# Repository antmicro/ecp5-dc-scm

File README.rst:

============
ECP5 DC-SCM
============

Copyright (c) 2020-2024 `Antmicro <https://www.antmicro.com>`_

.. image:: https://img.shields.io/badge/View%20on-Antmicro%20Open%20Source%20Portal-332d37?style=flat-square
      :target: https://opensource.antmicro.com/projects/ecp5-dc-scm

.. figure:: img/ecp5-dc-scm.png

Overview
--------

This repository contains design files of the experimental Data Center Secure Control Module (DC-SCM).
The main purpose of this platform is to provide open-source DC-SCM with Baseboard Management Controller (BMC) unit based on Lattice ECP5 FPGA family.
The design files were prepared in KiCad.
This design is now a Work in Progress.

Repository structure
--------------------
The main repository directory contains KiCad PCB project files, a LICENSE and README.
The remaining files are stored in the following directories:

* ``img`` - contains graphics for this README
* ``doc`` - contains schematics in pdf form
* ``assets`` - contains visual assets

Key Features
------------

* ECP5 FPGA - LFE5UM5G-85F-8BG756C
* DC-SCI standard 168-pin 4C+ edge connector
* On-board DDR3 DRAM and eMMC
* QSPI FLASH memory
* Gigabit Ethernet interface with KSZ9031RNXCA transciever
* JTAG connector
* M.2 (key M) connector with PCIe x4 interface
* 13 I2C buses, 4 I3C buses
* dual UART 
* 2x USB 2.0 host/device PHY (USB3300)
* SPI connector
* RoT module connector
* TPM SPI connector
* optional external 12V power input 

Block diagram
-------------

.. figure:: img/ecp5-dc-scm-diagram.png

License
=======

`Apache-2.0 <LICENSE>`_

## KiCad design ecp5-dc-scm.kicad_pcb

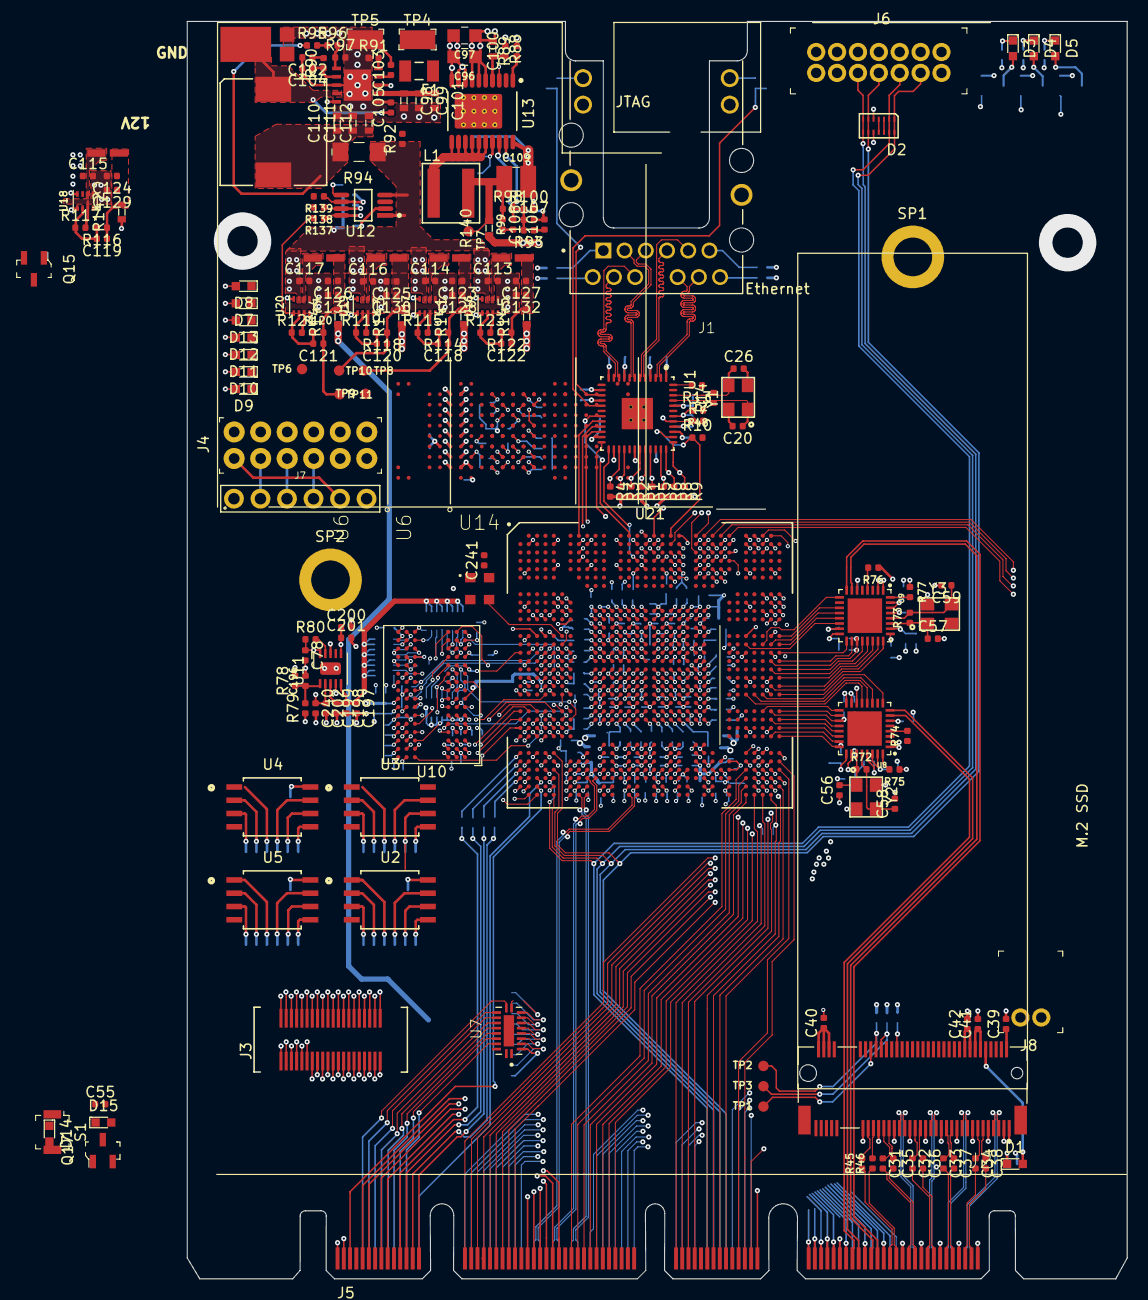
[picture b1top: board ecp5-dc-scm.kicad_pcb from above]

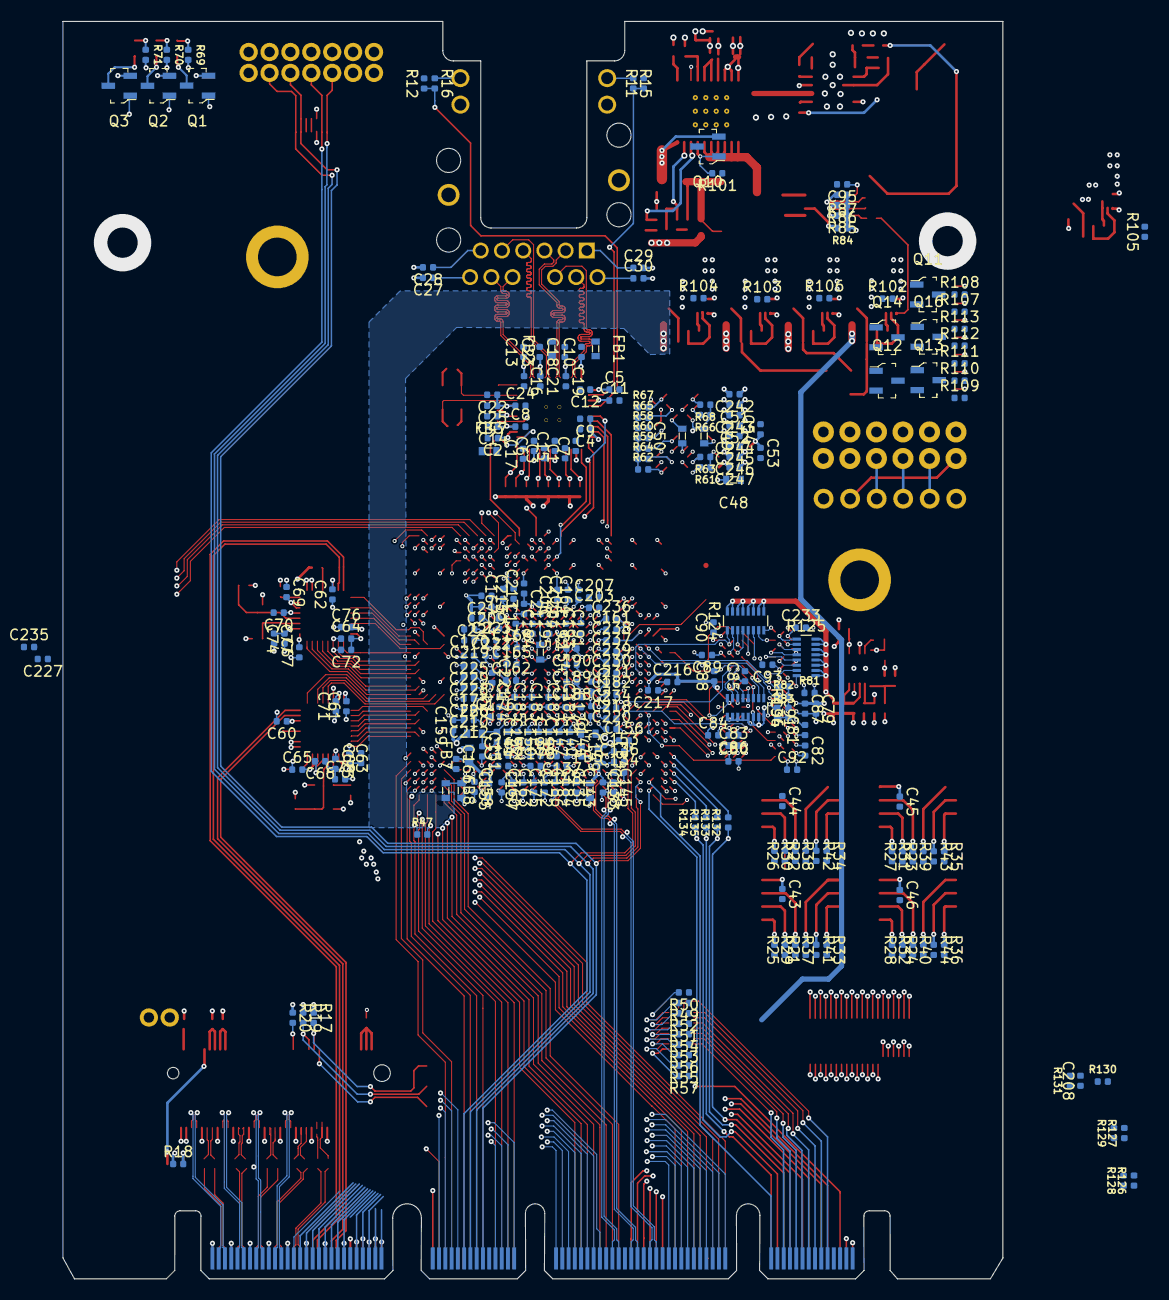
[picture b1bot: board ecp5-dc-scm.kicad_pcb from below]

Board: 8 copper layers, 90.0 x 120.4 mm, 481 parts (287 on the bottom side), 409 nets.

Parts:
C1, C6, C10, C18, C22, C53, C66, C68, C70, C72, C75, C77, C79, C134, C156, C158, C159, C160, C203, C209, C219, C225, C230, C235: C_4u7_0402; 0402-cap
C2, C3, C4, C8, C19, C43, C44, C45, C46, C80, C81, C82, C83, C84, C85, C86, C87, C89, C90, C91, C92, C135, C136, C161, C162, C163, C164, C165, C166, C167, C168, C170, C171, C173, C174, C176, C177, C179, C181, C182, C183, C184, C185, C186, C187, C188, C189, C190, C191, C192, C193, C194, C195, C204, C205, C206, C207, C210, C211, C212, C213, C214, C215, C218, C220, C221, C222, C223, C224, C226, C227, C228, C229, C231, C232, C233, C234, C236, C237, C238, C239: C_470n_0402; 0402-cap
C5, C7, C9, C11, C12, C13, C14, C15, C16, C17, C21, C23, C25, C95, C103, C138, C143, C144, C145, C146, C147, C172, C175: C_10n_0402; 0402-cap
C20, C26: C_22p_0402; 0402-cap
C24, C27, C28, C29, C30, C31, C32, C33, C34, C35, C36, C37, C38, C47, C51, C52, C54, C55, C60, C61, C62, C63, C64, C65, C67, C69, C71, C73, C74, C76, C88, C93, C94, C100, C105, C137, C139, C140, C141, C142, C169, C200, C201, C202, C208, C216, C217, C240, C241, C242, C243, C244, C245, C246, C247: C_100n_0402; 0402-cap
C39, C40, C41, C42, C78, C113, C114, C115, C116, C117, C123, C124, C125, C126, C127, C128, C129, C130, C131, C132, C197, C198, C199: C_10u_0402; 0402-cap
C48, C49, C50: C_22u_0603; 0603-cap
C56, C57, C58, C59: C_12p_0402; 0402-cap
C96, C97: C_10u_0805; 0805-cap
C98, C99, C101: C_2u2_0603_25V; 0603-cap
C102: C_4n7_0402; 0402-cap
C104: C_47p_0402; 0402-cap
C106: C_1n8_0402; 0402-cap
C107: C_180p_0402; 0402-cap
C108: C_750p_0402; 0402-res
C109: C_47u_1210; 1210-cap
C110, C111, C112, C133, C154, C155, C157: C_47u_0603; 0603-cap
C118, C119, C120, C121, C122: C_120p_0402; 0402-res
C148, C149, C150, C151, C152, C153, C178, C180, C196: C_1n_0402; 0402-res
D1: KP-1608CGCK; LED_0603
D2: TPD6E05U06
D3, D4, D5, D7, D8, D9, D10, D11, D12, D13, D14, D15: LG_L29K-G2J1-24-Z; LED_0603
D6: PDS760-13
F1: 0466003.NR; 1206-Fuse-Littelfuse-0466-0-0-MFG
FB1, FB2, FB3, FB4, FB5, FB6, FB7, FB8: BLM18PG121SN1D; 0603-res
IC1: TPS54561; WSON-10_4x4
J1: L834-1G1T-S7; BEL_L834-1G1T-S7
J2: 1-2199230-6
J3: 529910408
J4: M20-7830642; PinHeader_6x2_P2.54mm_Vertical
J5: SFF-TA-1002-4C+
J6: 0878311420; PinHeader_2x7_P2mm_Drill1mm
J7: 61300611121
J8: S2B-PH-K-S_LF__SN_; PinHeader_1x2_P2mm_Drill1mm_RA
L1: XAL5030-801; Coilcraft-XAL5030
L2: WE_7447798720
L3, L4, L5, L6, L7: IHLP1212AEERR47M11; IHLP-1212AE
Q1, Q2, Q3, Q10, Q11, Q12, Q13, Q14, Q15, Q16, Q17: 2N7002; SOT-23-3
R1, R2, R3, R4, R5, R6, R7, R8, R9, R10, R11, R12, R97: R_10k2_0402; 0402-res
R13: R_12k1_0402; 0402-res
R14: R_1M8_0402; 0402-res
R15, R16, R25, R26, R27, R28, R74, R76, R85, R86, R87, R107, R108, R109, R110, R111, R112, R113, R129, R130: R_1k_0402; 0402-res
R17, R19, R20, R29, R30, R31, R32, R33, R34, R35, R36, R37, R38, R39, R40, R41, R42, R43, R44, R58, R59, R60, R61, R62, R63, R64, R65, R66, R67, R68, R78, R79, R80, R98, R100, R101, R102, R103, R104, R105, R106, R126, R127, R131: R_10k_0402; 0402-res
R18: R_330R_0402; 0402-res
R21, R22, R23, R24, R48, R93: R_4k7_0402; 0402-res
R45, R46, R47, R132, R133, R134, R135, R137, R138, R139: R_0R_0402; 0402-res
R49, R50, R51, R52, R53, R54, R55, R56: R_357k_0402; 0402-res
R57, R116: R_200k_0402; 0402-res
R69, R70, R71, R84: R_1k1_0402; 0402-res
R72, R73: R_1M5_0402; 0402-res
R75, R77: R_12k_0402; 0402-res
R81: R_240R_0402; 0402-res
R82, R83: R_51R_0402; 0402-res
R88: R_10R_0603; 0603-res
R89: R_47k_0402; 0402-res
R90: R_16k9_0402; 0402-res
R91: R_243k_0402; 0402-res
R92, R115, R117, R119, R121, R123: R_100k_0402; 0402-res
R94: R_0R_1206; 1206-res
R95: R_49R9_0402; 0402-res
R96: R_53k6_0402; 0402-res
R99: R_470k_0402; 0402-res
R114, R122: R_453k_0402; 0402-res
R118: R_124k_0402; 0402-res
R120: R_66k5_0402; 0402-res
R124, R125, R136: 8x51R_0602_array; R_Array_Convex_8x0602
R128: R_22R_0402; 0402-res
R140, R141, R142, R143, R144, R145: R_0R_0603; 0603-res
S1: B3U-1000P; Switch_Tactile_SMD_B3U-1000P
SP1: 9774025151
SP2: 9774030151
TP1, TP2, TP3, TP6, TP7, TP8, TP9, TP10, TP11: TP_SMD1MM; Testpoint_smd_1mm
TP4, TP5: RCW-0C; PROBE_PAD_1206
U1: KSZ9031RNXCA; QFN-48-Microchip-QFN77-48LD-PL-2
U2, U3, U4, U5: W25Q32JVSSIQ_TR; W25Q32JVSSIQ
U6, U6#2: MTFC16GAPALNA-AIT; BGA100CP100_17X10_1800X1400X140B46N
U7: NVT2008DQ,115; QFN50P250X450X100-21N
U8, U9: USB3300-EZK-TR; QFN50P500X500X100-33N
U10: AS4C256M16D3; BGA-96_9.0x13.0mm_Layout2x3x16_P0.8mm
U11: TPS51200DRC; VSON-10-1EP_3x3mm
U12: LM3881MME_NOPB; VSSOP8-Texas_Instruments-DGK0008A
U13: LM21212-2; HTSSOP-20_TI-PWP
U14: AMJMEFB-100.0000T; AMJMEFB
U16, U17, U18, U19, U20: TPS62823DLCT; QFN-8_2x1mm
U21: ECP5UM5G_85_CABGA756; CABGA756_27x27mm_p0.8mm
Y1: ABM8G-25.000MHZ-18-D2Y-T; KX-7
Y2, Y3: TSX-3225; KX-7

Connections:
/DDR3/DDR3_VTT: C197.1, C198.1, C199.1, R124.9, R124.10, R124.11, R124.12, R124.13, R124.14, R124.15, R124.16, R125.9, R125.10, R125.11, R125.12, R125.13, R125.14, R125.15, R125.16, R136.9, R136.10, R136.11, R136.12, R136.13, R136.14, R136.15, R136.16, U11.3, U11.5
/Ethernet/AVDDL: C18.1, C19.1, C21.1, C23.1, FB2.1, U1.4, U1.9
/Ethernet/AVDDL_PLL: C22.1, C24.1, C25.1, FB3.1, U1.44
/Ethernet/ETH1_N: J1.10, U1.3
/Ethernet/ETH1_P: J1.11, U1.2
/Ethernet/ETH2_N: J1.5, U1.6
/Ethernet/ETH2_P: J1.4, U1.5
/Ethernet/ETH3_N: J1.2, U1.8
/Ethernet/ETH3_P: J1.3, U1.7
/Ethernet/ETH4_N: J1.9, U1.11
/Ethernet/ETH4_P: J1.8, U1.10
/Ethernet/ETH_LED1: R11.1, R15.2, U1.15
/Ethernet/ETH_LED2: R12.1, R16.2, U1.17
/FPGA power supply/VCCHTX0: C139.1, C144.1, C149.1, FB5.2, U21.AC13, U21.AC17
/FPGA power supply/VCCHTX1: C141.1, C146.1, C151.1, FB6.2, U21.AC16, U21.AC20
/Interfaces/1V0_EN: C55.2, R57.2, U7.2, U7.20
/Power supply/1V0_PG: Q11.1, R102.2, U20.8
/Power supply/1V2_PG: Q10.1, R101.2, U13.17
/Power supply/1V8_PG: Q15.1, R105.2, U18.8
/Power supply/1V35_PG: Q16.1, R106.2, U19.8
/Power supply/2V5_PG: Q14.1, R104.2, U16.8
/Power supply/3V3_PG: Q13.1, R103.2, U17.8
/Power supply/5V0_PG: IC1.10, R92.2
/Power supply/PWR_EN: Q12.1, R84.2, U12.2
/Power supply/VCCA0_EN: R137.2, U13.3, U20.1
/Power supply/VCCAUX_EN: R139.2, U16.1
/Power supply/VCCIO_EN: R138.2, U17.1, U18.1, U19.1
CLK_100M_PCIE_DN: J5.A13, U21.AM15
CLK_100M_PCIE_DP: J5.A12, U21.AM14
CLK_PCIE_x4_DN: J2.53, R46.2
CLK_PCIE_x4_DP: J2.55, R45.2
DDR3_A0: R136.1, U10.N3, U21.W4
DDR3_A1: R125.4, U10.P7, U21.V7
DDR3_A2: R124.3, U10.P3, U21.U7
DDR3_A3: R124.2, U10.N2, U21.AE6
DDR3_A4: R125.3, U10.P8, U21.R6
DDR3_A5: R124.4, U10.P2, U21.AE4
DDR3_A6: R125.2, U10.R8, U21.U6
DDR3_A7: R124.1, U10.R2, U21.U5
DDR3_A8: R125.1, U10.T8, U21.R7
DDR3_A9: R124.5, U10.R3, U21.R4
DDR3_A10: R125.7, U10.L7, U21.U4
DDR3_A11: R124.7, U10.R7, U21.T6
DDR3_A12: R125.5, U10.N7, U21.T5
DDR3_A13: R124.6, U10.T3, U21.T4
DDR3_A14: R124.8, U10.T7, U21.T7
DDR3_BA0: R136.7, U10.M2, U21.AC7
DDR3_BA1: R125.6, U10.N8, U21.V6
DDR3_BA2: R136.2, U10.M3, U21.W5
DDR3_CAS: R136.5, U10.K3, U21.W2
DDR3_CKE: R125.8, U10.K9, U21.Y1
DDR3_CLK+: R82.1, U10.J7, U21.P5
DDR3_CLK-: R83.2, U10.K7, U21.P4
DDR3_CS: R136.6, U10.L2, U21.R1
DDR3_DM0: U10.E7, U21.AD7
DDR3_DM1: U10.D3, U21.AC2
DDR3_DQ0: U10.E3, U21.AC6
DDR3_DQ1: U10.F7, U21.AD6
DDR3_DQ2: U10.F2, U21.Y4
DDR3_DQ3: U10.F8, U21.AE5
DDR3_DQ4: U10.H3, U21.AB7
DDR3_DQ5: U10.H8, U21.Y5
DDR3_DQ6: U10.G2, U21.Y6
DDR3_DQ7: U10.H7, U21.Y7
DDR3_DQ8: U10.D7, U21.AE3
DDR3_DQ9: U10.C3, U21.AE1
DDR3_DQ10: U10.C8, U21.AD3
DDR3_DQ11: U10.C2, U21.AB1
DDR3_DQ12: U10.A7, U21.AB4
DDR3_DQ13: U10.A2, U21.AC1
DDR3_DQ14: U10.B8, U21.AE2
DDR3_DQ15: U10.A3, U21.AD1
DDR3_DQS0+: U10.F3, U21.AB5
DDR3_DQS0-: U10.G3, U21.AB6
DDR3_DQS1+: U10.C7, U21.AC3
DDR3_DQS1-: U10.B7, U21.AB2
DDR3_ODT: R136.8, U10.K1, U21.AD4
DDR3_RAS: R136.4, U10.J3, U21.AB3
DDR3_RESET: U10.T2, U21.T2
DDR3_VREF: C88.1, C93.1, C200.1, C201.1, C216.2, C217.2, U10.H1, U10.M8, U11.6, U21.V4
DDR3_WE: R136.3, U10.L3, U21.AC5
DONE: R126.1, R128.1, U21.AJ4
ESPI_ALERT_N: J5.B3, U21.K30
ESPI_CLK: J5.B1, U21.L31
ESPI_CS0_N: J5.B2, U21.L32
ESPI_CS1_N: J5.B9, U21.H32
ESPI_IO0: J5.B5, U21.K32
ESPI_IO1: J5.B6, U21.K31
ESPI_IO2: J5.B7, U21.J32
ESPI_IO3: J5.B8, U21.H31
ESPI_RESET_N: J5.B4, U21.H30
ETH_INT_N: R10.1, U1.38, U21.A19
ETH_MDC: R8.1, U1.36, U21.B16
ETH_MDIO: R9.1, U1.37, U21.D17
ETH_~RESET: C47.1, R48.2, U1.42, U21.D18
GCLK100: U14.3, U21.N6
GND: C1.2, C2.2, C3.2, C4.2, C5.2, C6.2, C7.2, C8.2, C9.2, C10.2, C11.2, C12.2, C13.2, C14.2, C15.2, C16.2, C17.2, C18.2, C19.2, C20.2, C21.2, C22.2, C23.2, C24.2, C25.2, C26.2, C27.2, C28.2, C29.2, C30.2, C39.2, C40.2, C41.2, C42.2, C43.2, C44.2, C45.2, C46.2, C47.2, C48.2, C49.2, C50.2, C51.2, C52.2, C53.2, C54.2, C55.1, C56.2, C57.2, C58.2, C59.2, C60.1, C61.1, C62.1, C63.1, C64.1, C65.1, C66.1, C67.1, C68.2, C69.1, C70.1, C71.1, C72.2, C73.1, C74.1, C75.2, C76.1, C77.2, C78.2, C79.2, C80.2, C81.2, C82.2, C83.2, C84.2, C85.2, C86.2, C87.2, C88.2, C89.2, C90.2, C91.2, C92.2, C93.2, C94.1, C95.2, C96.2, C97.2, C98.2, C99.2, C100.2, C101.2, C102.2, C103.2, C104.2, C109.2, C110.2, C111.2, C112.2, C113.2, C114.2, C115.2, C116.2, C117.2, C123.2, C124.2, C125.2, C126.2, C127.2, C128.2, C129.2, C130.2, C131.2, C132.2, C133.2, C134.2, C135.2, C136.2, C137.2, C138.2, C139.2, C140.2, C141.2, C142.2, C143.2, C144.2, C145.2, C146.2, C147.2, C148.2, C149.2, C150.2, C151.2, C152.2, C153.2, C154.2, C155.2, C156.2, C157.2, C158.2, C159.2, C160.2, C161.2, C162.2, C163.2, C164.2, C165.2, C166.2, C167.2, C168.2, C169.2, C170.2, C171.2, C172.2, C173.2, C174.2, C175.2, C176.2, C177.2, C178.2, C179.2, C180.2, C181.2, C182.2, C183.2, C184.2, C185.2, C186.2, C187.2, C188.2, C189.2, C190.2, C191.2, C192.2, C193.2, C194.2, C195.2, C196.2, C197.2, C198.2, C199.2, C200.2, C201.2, C202.2, C203.2, C204.2, C205.2, C206.2, C207.2, C208.1, C209.2, C210.2, C211.2, C212.2, C213.2, C214.2, C215.2, C216.1, C217.1, C218.2, C219.2, C220.2, C221.2, C222.2, C223.2, C224.2, C225.2, C226.2, C227.2, C228.2, C229.2, C230.2, C231.2, C232.2, C233.2, C234.2, C235.2, C236.2, C237.2, C238.2, C239.2, C240.2, C241.2, C242.2, C243.2, C244.2, C245.2, C246.2, C247.2, D2.5, D2.10, D6.A, IC1.8, IC1.11, J1.13, J1.15, J1.S1, J1.S2, J2.1, J2.3, J2.9, J2.15, J2.21, J2.27, J2.33, J2.39, J2.45, J2.51, J2.57, J2.71, J2.73, J2.75, J2.SH1, J2.SH2, J3.1, J4.5, J4.11, J5.A11, J5.A14, J5.A17, J5.A20, J5.A33, J5.A42, J5.A58, J5.A61, J5.A64, J5.A67, J5.A70, J5.B10, J5.B17, J5.B26, J5.B33, J5.B38, J5.B49, J5.B52, J5.B55, J5.B58, J5.B61, J5.B64, J5.B67, J5.B70, J5.OA3, J5.OA4, J5.OA13, J5.OB4, J5.OB7, J5.OB10, J6.1, J6.3, J6.5, J6.7, J6.9, J6.11, J6.13, J7.6, J8.2, Q1.2, Q2.2, Q3.2, Q10.2, Q11.2, Q12.2, Q13.2, Q14.2, Q15.2, Q16.2, Q17.2, R13.1, R75.1, R77.1, R78.2, R81.2, R89.2, R91.1, R97.2, R100.2, R115.2, R117.2, R119.2, R121.2, R123.2, S1.2, TP5.1, U1.29, U1.49, U2.4, U3.4, U4.4, U5.4, U6#2.G2, U6#2.G3, U6#2.G4, U6#2.G5, U6#2.G6, U6#2.G7, U6#2.G8, U6#2.G9, U6#2.H2, U6#2.H9, U6#2.J5, U6#2.L3, U6#2.L8, U6#2.M4, U6#2.M7, U6#2.P2, U6#2.P9, U7.1, U8.1, U8.2, U8.33, U9.1, U9.2, U9.33, U10.A9, U10.B1, U10.B3, U10.B9, U10.D1, U10.D8, U10.E1, U10.E2, U10.E8, U10.F9, U10.G1, U10.G8, U10.G9, U10.J2, U10.J8, U10.M1, U10.M9, U10.P1, U10.P9, U10.T1, U10.T9, U11.4, U11.8, U11.11, U12.3, U13.8, U13.9, U13.10, U13.20, U13.21, U14.2, U16.3, U16.5, U17.3, U17.5, U18.3, U18.5, U19.3, U19.5, U20.3, U20.5, U21.AA11, U21.AA22, U21.AB11, U21.AB12, U21.AB13, U21.AB14, U21.AB15, U21.AB16, U21.AB17, U21.AB18, U21.AB19, U21.AB20, U21.AB21, U21.AB22, U21.AC12, U21.AC21, U21.AD2, U21.AD5, U21.AD28, U21.AD31, U21.AF11, U21.AF12, U21.AF14, U21.AF15, U21.AF16, U21.AF17, U21.AF19, U21.AF20, U21.AF23, U21.AG11, U21.AG14, U21.AG15, U21.AG16, U21.AG17, U21.AG20, U21.AG23, U21.AH2, U21.AH5, U21.AH7, U21.AH8, U21.AH11, U21.AH14, U21.AH15, U21.AH16, U21.AH17, U21.AH20, U21.AH23, U21.AH24, U21.AH25, U21.AH26, U21.AH29, U21.AH31, U21.AJ7, U21.AJ8, U21.AJ11, U21.AJ14, U21.AJ17, U21.AJ20, U21.AJ23, U21.AJ26, U21.AK7, U21.AK8, U21.AK11, U21.AK14, U21.AK17, U21.AK20, U21.AK23, U21.AK26, U21.AL2, U21.AL5, U21.AL7, U21.AL8, U21.AL9, U21.AL11, U21.AL12, U21.AL14, U21.AL15, U21.AL17, U21.AL18, U21.AL20, U21.AL21, U21.AL23, U21.AL24, U21.AL26, U21.AL29, U21.AL31, U21.AM7, U21.AM26, U21.B2, U21.B5, U21.B9, U21.B13, U21.B15, U21.B18, U21.B20, U21.B24, U21.B28, U21.B31, U21.C30, U21.E2, U21.E5, U21.E9, U21.E13, U21.E15, U21.E18, U21.E20, U21.E24, U21.E28, U21.E31, U21.J2, U21.J5, U21.J28, U21.J31, U21.K10, U21.K11, U21.K22, U21.K23, U21.L10, U21.L11, U21.L12, U21.L13, U21.L14, U21.L15, U21.L16, U21.L17, U21.L18, U21.L19, U21.L20, U21.L21, U21.L22, U21.L23, U21.M11, U21.M22, U21.N2, U21.N5, U21.N11, U21.N13, U21.N14, U21.N15, U21.N16, U21.N17, U21.N18, U21.N19, U21.N20, U21.N22, U21.N28, U21.N31, U21.P11, U21.P13, U21.P14, U21.P15, U21.P16, U21.P17, U21.P18, U21.P19, U21.P20, U21.P22, U21.R2, U21.R5, U21.R11, U21.R13, U21.R14, U21.R15, U21.R16, U21.R17, U21.R18, U21.R19, U21.R20, U21.R22, U21.R28, U21.R31, U21.T11, U21.T13, U21.T14, U21.T15, U21.T16, U21.T17, U21.T18, U21.T19, U21.T20, U21.T22, U21.U11, U21.U13, U21.U14, U21.U15, U21.U16, U21.U17, U21.U18, U21.U19, U21.U20, U21.U22, U21.V2, U21.V5, U21.V11, U21.V13, U21.V14, U21.V15, U21.V16, U21.V17, U21.V18, U21.V19, U21.V20, U21.V22, U21.V28, U21.V31, U21.W11, U21.W13, U21.W14, U21.W15, U21.W16, U21.W17, U21.W18, U21.W19, U21.W20, U21.W22, U21.Y2, U21.Y11, U21.Y13, U21.Y14, U21.Y15, U21.Y16, U21.Y17, U21.Y18, U21.Y19, U21.Y20, U21.Y22, U21.Y31, Y1.2, Y1.4, Y2.2, Y2.4, Y3.2, Y3.4
I2C[0]_SCL: J5.A1, U21.E25
I2C[0]_SDA: J5.A2, U21.D26
I2C[1]_SCL: J5.A3, U21.E22
I2C[1]_SDA: J5.A4, U21.E23
I2C[2]_SCL: J5.A5, U21.D22
I2C[2]_SDA: J5.A6, U21.D23
I2C[3]_SCL: J5.A7, U21.D25
I2C[3]_SDA: J5.A8, U21.D24
I2C[4]_SCL: J5.A9, U21.C26
I2C[4]_SDA: J5.A10, U21.B29
I2C[5]_SCL: J5.A21, U21.A31
I2C[5]_SDA: J5.A22, U21.B30
I2C[6]_SCL: J5.A23, U21.A30
I2C[6]_SDA: J5.A24, U21.A29
I2C[7]_SCL: J5.A25, U21.A28
I2C[7]_SDA: J5.A26, U21.C25
I2C[8]_SCL: J5.A27, U21.B25
I2C[8]_SDA: J5.A28, U21.B26
I2C[9]_SCL: J5.A29, U21.C23
I2C[9]_SDA: J5.A30, U21.C24
I2C[10]_SCL: J5.A31, U21.B23
I2C[10]_SDA: J5.A32, U21.B22
I2C[11]_SCL: J5.A38, U21.A26
I2C[11]_SDA: J5.A39, U21.A25
I2C[12]_SCL: J5.A40, U21.A24
I2C[12]_SDA: J5.A41, U21.A23
I3C[0]_SCL_1V0: J5.OA5, U7.11
I3C[0]_SCL_3V3: R50.2, U7.10, U21.A20
I3C[0]_SDA_1V0: J5.OA6, U7.12
I3C[0]_SDA_3V3: R49.2, U7.9, U21.C19
I3C[1]_SCL_1V0: J5.OA7, U7.13
I3C[1]_SCL_3V3: R52.2, U7.8, U21.F20
I3C[1]_SDA_1V0: J5.OA8, U7.14
I3C[1]_SDA_3V3: R51.2, U7.7, U21.D19
I3C[2]_SCL_1V0: J5.OA9, U7.15
I3C[2]_SCL_3V3: R54.2, U7.6, U21.E19
I3C[2]_SDA_1V0: J5.OA10, U7.16
I3C[2]_SDA_3V3: R53.2, U7.5, U21.F19
I3C[3]_SCL_1V0: J5.OA11, U7.17
I3C[3]_SCL_3V3: R56.2, U7.4, U21.D20
I3C[3]_SDA_1V0: J5.OA12, U7.18
I3C[3]_SDA_3V3: R55.2, U7.3, U21.C20
INIT_N: D14.2, J3.19, R127.1, U21.AG4
JTAG_TCK: D2.13, J5.A34, J6.6, U21.AK5
JTAG_TDI: D2.8, J5.A36, J6.10, U21.AJ5
JTAG_TDO: D2.9, J5.A37, J6.8, U21.AG5
JTAG_TMS: D2.14, J5.A35, J6.4, U21.AM5
MMC_CLK: R58.2, U6#2.P6, U21.P6
MMC_CMD: R60.2, U6#2.P5, U21.J7
MMC_DAT0: R61.2, U6#2.K2, U21.N4
MMC_DAT1: R62.2, U6#2.N2, U21.L7
MMC_DAT2: R63.2, U6#2.K3, U21.N3
MMC_DAT3: R64.2, U6#2.N3, U21.L4
MMC_DAT4: R65.2, U6#2.N8, U21.K7
MMC_DAT5: R66.2, U6#2.K8, U21.K5
MMC_DAT6: R67.2, U6#2.N9, U21.K6
MMC_DAT7: R68.2, U6#2.K9, U21.J6
MMC_RSTN: R59.2, U6#2.M5, U21.L3
NCSI_CLK: J5.B18, U21.AJ28
NCSI_CRS_DV: J5.B19, U21.AK28
NCSI_RXD0: J5.B24, U21.AJ29
NCSI_RXD1: J5.B25, U21.AK29
NCSI_RXER: J5.B23, U21.AH30
NCSI_TXD0: J5.B21, U21.AM28
NCSI_TXD1: J5.B22, U21.AH28
NCSI_TXEN: J5.B20, U21.AL28
unnamed: C10.1, C13.1, C16.1, FB1.2, U1.1, U1.12
unnamed: C20.1, R14.1, U1.45, Y1.1
unnamed: C26.1, R14.2, U1.46, Y1.3
unnamed: C27.1, J1.12
unnamed: C28.1, J1.6
unnamed: C29.1, J1.1
unnamed: C30.1, J1.7
unnamed: C31.1, J2.49
unnamed: C32.1, J2.37
unnamed: C33.1, J2.25
unnamed: C34.1, J2.13
unnamed: C35.1, J2.47
unnamed: C36.1, J2.35
unnamed: C37.1, J2.23
unnamed: C38.1, J2.11
unnamed: C53.1, C54.1, U6#2.E4
unnamed: C56.1, R72.1, U8.27, Y2.1
unnamed: C57.1, R73.1, U9.27, Y3.1
unnamed: C58.1, R72.2, U8.28, Y2.3
unnamed: C59.1, R73.2, U9.28, Y3.3
unnamed: C66.2, U8.29
unnamed: C70.2, U9.29
unnamed: C94.2, R82.2, R83.1
unnamed: C95.1, U12.5
unnamed: C100.1, R88.2, U13.4
unnamed: C102.1, R90.2
unnamed: C103.1, IC1.4
unnamed: C104.1, IC1.7, R90.1
unnamed: C105.1, D6.C, IC1.9, L2.1
unnamed: C105.2, IC1.1
unnamed: C106.1, R93.1
unnamed: C106.2, C107.2, U13.18
unnamed: C107.1, R93.2, R98.2, R99.2, R100.1, U13.19
unnamed: C108.1, C109.1, L1.2, R98.1, R140.2, TP7.1
unnamed: C108.2, R99.1
unnamed: C110.1, C111.1, C112.1, L2.2, R94.2, R95.1
unnamed: C118.1, C123.1, C128.1, L3.2, R114.1, R141.2, TP8.1
unnamed: C118.2, R114.2, R115.1, U17.2
unnamed: C119.1, C124.1, C129.1, L4.2, R116.1, R142.2, TP9.1
unnamed: C119.2, R116.2, R117.1, U18.2
unnamed: C120.1, C125.1, C130.1, L5.2, R118.1, R143.2, TP10.1
unnamed: C120.2, R118.2, R119.1, U19.2
unnamed: C121.1, C126.1, C131.1, L6.2, R120.2, R144.2, TP11.1
unnamed: C121.2, R120.1, R121.1, U20.2
unnamed: C122.1, C127.1, C132.1, L7.2, R122.1, R145.2
unnamed: C122.2, R122.2, R123.1, U16.2
unnamed: C196.1, R78.1, R79.2, U11.1
unnamed: D1.1, R18.2
unnamed: D1.2, J2.10
unnamed: D3.1, R69.1
unnamed: D3.2, Q1.3
unnamed: D4.1, R70.1
unnamed: D4.2, Q2.3
unnamed: D5.1, R71.1
unnamed: D5.2, Q3.3
unnamed: D7.2, R107.2
unnamed: D8.2, R108.2
unnamed: D9.2, R109.2
unnamed: D10.2, R110.2
unnamed: D11.2, R111.2
unnamed: D12.2, R112.2
unnamed: D13.2, R113.2
unnamed: D14.1, R129.2
unnamed: D15.1, R130.2
unnamed: D15.2, Q17.3
unnamed: IC1.3, TP6.1
unnamed: IC1.5, R91.2
unnamed: IC1.6, R96.2, R97.1
unnamed: J1.14, R15.1
unnamed: J1.16, R16.1
unnamed: J2.44, R20.2
unnamed: J2.52, R17.2, TP2.1
unnamed: J2.54, TP1.1
unnamed: J5.B56, R45.1
unnamed: J5.B57, R46.1
unnamed: L1.1, U13.11, U13.12, U13.13, U13.14, U13.15, U13.16
unnamed: L3.1, U17.6
unnamed: L4.1, U18.6
unnamed: L5.1, U19.6
unnamed: L6.1, U20.6
unnamed: L7.1, U16.6
unnamed: Q10.3, R107.1
unnamed: Q11.3, R108.1
unnamed: Q12.3, R109.1
unnamed: Q13.3, R110.1
unnamed: Q14.3, R111.1
unnamed: Q15.3, R112.1
unnamed: Q16.3, R113.1
unnamed: Q17.1, R128.2
unnamed: R13.2, U1.48
unnamed: R74.2, U8.4
unnamed: R75.2, U8.32
unnamed: R76.2, U9.4
unnamed: R77.2, U9.32
unnamed: R80.2, U11.9
unnamed: R81.1, U10.L8
unnamed: R89.1, U13.1
unnamed: R95.2, R96.1
unnamed: R132.2, U21.AG1
unnamed: R133.2, U21.AH1
unnamed: R134.2, U21.AK1
unnamed: R135.2, U21.AJ1
unnamed: R85.2, R137.1, U12.8
unnamed: R86.2, R138.1, U12.7
unnamed: R87.2, R139.1, U12.6
P12V_AUX: F1.1, J5.OA1, J5.OA2, J5.OB1, J5.OB2
PCIE_BMC_RX_DN: J5.A19, U21.AM9
PCIE_BMC_RX_DP: J5.A18, U21.AM8
PCIE_BMC_TX_DN: J5.A16, U21.AK10
PCIE_BMC_TX_DP: J5.A15, U21.AK9
PCIE_HPM_RXN[0]: J2.41, J5.A60
PCIE_HPM_RXN[1]: J2.29, J5.A63
PCIE_HPM_RXN[2]: J2.17, J5.A66
PCIE_HPM_RXN[3]: J2.5, J5.A69
PCIE_HPM_RXP[0]: J2.43, J5.A59
PCIE_HPM_RXP[1]: J2.31, J5.A62
PCIE_HPM_RXP[2]: J2.19, J5.A65
PCIE_HPM_RXP[3]: J2.7, J5.A68
PCIE_HPM_TXN[0]: C35.2, J5.B60
PCIE_HPM_TXN[1]: C36.2, J5.B63
PCIE_HPM_TXN[2]: C37.2, J5.B66
PCIE_HPM_TXN[3]: C38.2, J5.B69
PCIE_HPM_TXP[0]: C31.2, J5.B59
PCIE_HPM_TXP[1]: C32.2, J5.B62
PCIE_HPM_TXP[2]: C33.2, J5.B65
PCIE_HPM_TXP[3]: C34.2, J5.B68
PROGRAM_N: C208.2, J3.18, R131.1, S1.1, U21.AH4
PRSNT0_N: J2.50, J5.OB3, R19.2, TP3.1, U21.AL3
QSPI0_CLK: J3.7, J5.B11
QSPI0_CS0_N: J3.8, J5.B12
QSPI0_CS1_N: J3.22, J5.B42
QSPI0_D0: J3.9, J5.B13
QSPI0_D1: J3.10, J5.B14
QSPI0_D2: J3.11, J5.B15
QSPI0_D3: J3.12, J5.B16
QSPI1_CLK: J5.B43, U21.AJ31
QSPI1_CS0_N: J5.B44, U21.AK32
QSPI1_D0: J5.B45, U21.AG28
QSPI1_D1: J5.B46, U21.AG29
QSPI1_D2: J5.B47, U21.AG30
QSPI1_D3: J5.B48, U21.AG32
QSPIA1_CS_N: J3.4, R24.2, U5.1
QSPIA1_D0: J3.6, R32.1, U5.5
QSPIA1_D1: J3.3, R44.1, U5.2
QSPIA1_D2: J3.2, R36.1, U5.3
QSPIA1_D3: J3.5, R40.1, U5.7
QSPIA2_CS_N: J3.25, R23.2, U4.1
QSPIA2_D0: J3.28, R31.1, U4.5
QSPIA2_D1: J3.24, R43.1, U4.2
QSPIA2_D2: J3.23, R35.1, U4.3
QSPIA2_D3: J3.26, R39.1, U4.7
QSPIA_CLK: J3.27, R27.2, R28.2, U4.6, U5.6
QSPIB1_CS_N: J3.31, R22.2, U3.1
QSPIB1_D0: J3.33, R30.1, U3.5
QSPIB1_D1: J3.30, R42.1, U3.2
QSPIB1_D2: J3.29, R34.1, U3.3
QSPIB1_D3: J3.32, R38.1, U3.7
QSPIB2_CS_N: J3.36, R21.2, U2.1
QSPIB2_D0: J3.39, R29.1, U2.5
QSPIB2_D1: J3.35, R41.1, U2.2
QSPIB2_D2: J3.34, R33.1, U2.3
QSPIB2_D3: J3.37, R37.1, U2.7
QSPIB_CLK: J3.38, R25.2, R26.2, U2.6, U3.6
RGMII_REF_CLK: R7.1, U1.41, U21.B17
RGMII_RXD0: R1.1, U1.32, U21.A16
RGMII_RXD1: R2.1, U1.31, U21.D16
RGMII_RXD2: R3.1, U1.28, U21.E16
RGMII_RXD3: R4.1, U1.27, U21.C8
RGMII_RX_CLK: R6.1, U1.35, U21.A17
RGMII_RX_DV: R5.1, U1.33, U21.C16
RGMII_TXD0: U1.19, U21.A14
RGMII_TXD1: U1.20, U21.A8
RGMII_TXD2: U1.21, U21.B8
RGMII_TXD3: U1.22, U21.D8
RGMII_TX_CLK: U1.24, U21.C17
RGMII_TX_EN: U1.25, U21.D15
ROT_QSPI_CS_N: J3.40, U21.AG3
ROT_QSPI_DQ0: J3.17, U21.AK2
ROT_QSPI_DQ1: J3.16, U21.AJ2
ROT_QSPI_DQ2: J3.15, U21.AM2
ROT_QSPI_DQ3: J3.14, U21.AL1
ROT_QSPI_SCK: J3.13, U21.AM3
SGPIO0_CLK: J5.B30, R47.2, U21.AK30
SGPIO0_DI: J5.B31, U21.AM30
SGPIO0_DO: J5.B29, U21.AM29
SGPIO0_LD: J5.B32, U21.AL30
SGPIO1_CLK: J5.B35, R47.1, U21.AM31
SGPIO1_DI: J5.B36, U21.AK31
SGPIO1_DO: J5.B34, U21.AJ30
SGPIO1_LD: J5.B37, U21.AL32
SGPIO_INTR_N: J5.B40, U21.AH32
SGPIO_RESET_N: J5.B39, U21.AJ32
SPI0_CLK: J4.4, J5.OB11, J7.4, R132.1
SPI0_CS_N: J4.1, J5.OB12, J7.5, R133.1
SPI0_MISO: J4.3, J5.OB14, J7.3, R135.1
SPI0_MOSI: J4.2, J5.OB13, J7.2, R134.1
UART0_SCM_RX: J5.OB9, U21.F25
UART0_SCM_TX: J5.OB8, U21.F24
UART1_SCM_RX: J5.OB6, U21.F23
UART1_SCM_TX: J5.OB5, U21.F22
ULPI1_CLKO: U9.14, U21.P28
ULPI1_D0: U9.24, U21.W31
ULPI1_D1: U9.23, U21.W32
ULPI1_D2: U9.22, U21.V32
ULPI1_D3: U9.21, U21.U31
ULPI1_D4: U9.20, U21.U32
ULPI1_D5: U9.19, U21.T31
ULPI1_D6: U9.18, U21.T32
ULPI1_D7: U9.17, U21.R32
ULPI1_DIR: U9.12, U21.P31
ULPI1_NXT: U9.11, U21.N32
ULPI1_RESET: U9.9, U21.P30
ULPI1_STP: U9.13, U21.P32
ULPI2_CLKO: U8.14, U21.R26
ULPI2_D0: U8.24, U21.AE32
ULPI2_D1: U8.23, U21.AE31
ULPI2_D2: U8.22, U21.AD32
ULPI2_D3: U8.21, U21.AC31
ULPI2_D4: U8.20, U21.AC32
ULPI2_D5: U8.19, U21.AB31
ULPI2_D6: U8.18, U21.AB32
ULPI2_D7: U8.17, U21.AB30
ULPI2_NXT: U8.11, U21.Y30
ULPI2_RESET: U8.9, U21.Y32
ULPI2_STP: U8.13, U21.Y28
ULPI_DIR: U8.12, U21.Y29
USB1_DN: J5.B54, U9.8
USB1_DP: J5.B53, U9.7
USB2_DN: J5.B51, U8.8
USB2_DP: J5.B50, U8.7
USR_LED0: Q1.1, U21.B19
USR_LED1: Q2.1, U21.C22
USR_LED2: Q3.1, U21.A22
VCC1V0: R102.1, R144.1, U7.19
VCC1V2: C1.1, C2.1, C3.1, C4.1, C5.1, C7.1, C9.1, C12.1, C15.1, C154.1, C156.1, C159.1, C162.1, C165.1, C168.1, C171.1, C174.1, C177.1, C181.1, C183.1, C185.1, C187.1, C188.1, C189.1, C190.1, C191.1, C192.1, C193.1, C194.1, C195.1, FB2.2, FB3.2, FB4.1, FB5.1, FB6.1, FB7.2, R101.1, R140.1, U1.14, U1.23, U1.26, U1.30, U1.39, U21.AA12, U21.AA13, U21.AA14, U21.AA15, U21.AA16, U21.AA17, U21.AA18, U21.AA19, U21.AA20, U21.AA21, U21.M12, U21.M13, U21.M14, U21.M15, U21.M16, U21.M17, U21.M18, U21.M19, U21.M20, U21.M21, U21.N12, U21.N21, U21.P12, U21.P21, U21.R12, U21.R21, U21.T12, U21.T21, U21.U12, U21.U21, U21.V12, U21.V21, U21.W12, U21.W21, U21.Y12, U21.Y21
VCC1V8: C71.2, C73.2, C74.2, C75.1, C76.2, C77.1, C219.1, C221.1, C222.1, C223.1, C224.1, R20.1, R105.1, R142.1, U8.15, U8.26, U9.15, U9.26, U21.M23, U21.P23, U21.R23, U21.T23
VCC1V35: C79.1, C80.1, C81.1, C82.1, C83.1, C84.1, C85.1, C86.1, C87.1, C89.1, C90.1, C91.1, C92.1, C202.1, C230.1, C231.1, C232.1, C233.1, C234.1, C240.1, R79.1, R106.1, R143.1, U10.A1, U10.A8, U10.B2, U10.C1, U10.C9, U10.D2, U10.D9, U10.E9, U10.F1, U10.G7, U10.H2, U10.H9, U10.K2, U10.K8, U10.N1, U10.N9, U10.R1, U10.R9, U11.2, U21.AA10, U21.U10, U21.V10, U21.W10
VCC2V5: FB8.2, R104.1, R145.1
VCC3V3: C6.1, C8.1, C11.1, C14.1, C17.1, C39.1, C40.1, C41.1, C42.1, C43.1, C44.1, C45.1, C46.1, C48.1, C49.1, C50.1, C51.1, C52.1, C60.2, C61.2, C62.2, C63.2, C64.2, C65.2, C67.2, C68.1, C69.2, C72.1, C78.1, C203.1, C204.1, C205.1, C206.1, C207.1, C209.1, C210.1, C211.1, C212.1, C213.1, C214.1, C215.1, C218.1, C220.1, C225.1, C226.1, C227.1, C228.1, C229.1, C235.1, C236.1, C237.1, C238.1, C239.1, C242.1, C243.1, C244.1, C245.1, C246.1, C247.1, D7.1, D8.1, D9.1, D10.1, D11.1, D12.1, D13.1, FB1.1, J2.2, J2.4, J2.12, J2.14, J2.16, J2.18, J2.70, J2.72, J2.74, J3.21, J4.6, J4.12, J6.2, J7.1, R1.2, R2.2, R3.2, R4.2, R5.2, R6.2, R7.2, R8.2, R9.2, R10.2, R11.2, R12.2, R17.1, R18.1, R19.1, R21.1, R22.1, R23.1, R24.1, R25.1, R26.1, R27.1, R28.1, R29.2, R30.2, R31.2, R32.2, R33.2, R34.2, R35.2, R36.2, R37.2, R38.2, R39.2, R40.2, R41.2, R42.2, R43.2, R44.2, R48.1, R49.1, R50.1, R51.1, R52.1, R53.1, R54.1, R55.1, R56.1, R57.1, R58.1, R59.1, R60.1, R61.1, R62.1, R63.1, R64.1, R65.1, R66.1, R67.1, R68.1, R69.2, R70.2, R71.2, R80.1, R103.1, R126.2, R127.2, R129.1, R130.1, R131.2, R141.1, U1.16, U1.34, U1.40, U2.8, U3.8, U4.8, U5.8, U6#2.F2, U6#2.F3, U6#2.F4, U6#2.F5, U6#2.F6, U6#2.F7, U6#2.F8, U6#2.F9, U6#2.H3, U6#2.H8, U6#2.L2, U6#2.L4, U6#2.L7, U6#2.L9, U6#2.P3, U6#2.P8, U8.6, U8.16, U8.25, U8.30, U8.31, U9.6, U9.16, U9.25, U9.30, U9.31, U11.10, U14.1, U21.AA23, U21.AB10, U21.AB23, U21.AC10, U21.AC23, U21.K12, U21.K14, U21.K15, U21.K16, U21.K17, U21.K18, U21.K19, U21.K21, U21.M10, U21.P10, U21.R10, U21.T10, U21.U23, U21.V23, U21.W23
VCC3V3_T: C241.1, U14.4
VCC5V0: C96.1, C97.1, C113.1, C114.1, C115.1, C116.1, C117.1, R74.1, R76.1, R84.1, R85.1, R86.1, R87.1, R88.1, R92.1, R94.1, U12.1, U12.4, U13.5, U13.6, U13.7, U16.7, U17.7, U18.7, U19.7, U20.7
VCC12V: C98.1, C99.1, C101.1, F1.2, IC1.2, TP4.1
VCCA0: C133.1, C134.1, C135.1, C136.1, C137.1, C138.1, C140.1, C143.1, C145.1, C148.1, C150.1, C153.1, FB4.2, U21.AC14, U21.AC18, U21.AG9, U21.AG12, U21.AH9, U21.AH12, U21.AJ9, U21.AJ10, U21.AJ12, U21.AJ13
VCCA1: C142.1, C147.1, C152.1, C157.1, C160.1, C163.1, C166.1, C169.1, C172.1, C175.1, C178.1, C180.1, FB7.1, U21.AC15, U21.AC19, U21.AF22, U21.AG19, U21.AG22, U21.AH19, U21.AH22, U21.AJ18, U21.AJ19, U21.AJ21, U21.AJ22
VCCAUX: C155.1, C158.1, C161.1, C164.1, C167.1, C170.1, C173.1, C176.1, C179.1, C182.1, C184.1, C186.1, FB8.1, U21.AC11, U21.AC22, U21.AJ15, U21.AJ16, U21.AJ24, U21.AJ25, U21.K13, U21.K20, U21.N10, U21.N23, U21.Y10, U21.Y23
VIRTUAL_RESEAT: J5.OA14, U21.AK3

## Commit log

2020-12-01 Add basic README.rst
2020-12-01 Create project
2020-12-01 Add gitignore
2020-12-01 Add FPGA banks schematic
2020-12-02 Add FPGA power supply sheet
2020-12-03 Add ethernet schematic sheet
2020-12-03 Clean up designators
2020-12-04 Add power-supply schematic sheet-WIP
2020-12-07 Add missing components
2020-12-07 Change power supply schematic - WIP
2020-12-07 Connect RGMII to FPGA
2020-12-07 Update main schematic file
2020-12-07 Add DDR3 schematic sheet
2020-12-07 Connect DDR3 to FPGA
2020-12-08 Added flash, added interface labels to FPGA banks sheet
2020-12-08 Added Interfaces sheet for debug and other IO connectors
2020-12-08 Add edge connector sheet
2020-12-09 Cleaned up connections
2020-12-09 Added draft sheet for RoT connector
2020-12-09 Added M.2 connector
2020-12-10 Add 1V0 power supply and sequencer
2020-12-10 SPI and QSPI mostly done (to be verified)
2020-12-10 Fix capacitors reference
2020-12-10 Added preliminary power sequencer for RoT, HPM and FPGA
2020-12-10 Add I3C voltage level translation
2020-12-11 Edit in power sequencer
2020-12-11 Add PCB outline
2020-12-12 Fix I3C labels names
2020-12-12 Add initial component placement
2020-12-12 Added TPM SPI connector
2020-12-13 Update PCB layout
2020-12-13 Clean up main schematic file
2020-12-13 Update power-supply sheet
2020-12-13 Replace DDR3 memory
2020-12-13 Removed inverters
2020-12-13 Moved eSPI interface
2020-12-13 Updated supplies connections
2020-12-14 Clean up main sch file
    Separate power supply schematic
2020-12-14 Update all schematic designators
2020-12-14 Fix designators
2020-12-14 Add ethernet and power supply component placement
2020-12-14 Fix outline
2020-12-14 Close PCB outline
2020-12-14 Add flash components placement
2020-12-14 Add DDR3 passives initial placement
2020-12-15 Added block diagram
2020-12-15 Updated outline and 3D models
2020-12-15 Added 3D vis
2020-12-15 Add local component libraries.
2020-12-15 Updated 3D vis
2020-12-15 Updated PCIe connection
2020-12-15 Diagram update
2020-12-15 README: minor fix
2020-12-15 Add power supply placement and initial routing
2020-12-15 Remove DC jack connector
2020-12-16 Add changes to power supply sheet
    Added 1k pullup to 3V3 on PWR_EN signal
    Tied PWR_EN directly to its transistor’s gate, removed 10k pullup there
    R69 package changed to 1206
    Replaced DC jack with RCW-0C testpads (1206), tied P12V_AUX with 12V0
2020-12-16 Combine two power supply sheets into one
2020-12-16 1v2 power supply component placement
2020-12-16 Add PCIe passives placement
2020-12-17 Remove I2C and I3C goldpin connectors
2020-12-17 Add power supply component placement -WIP
2020-12-17 Add component placement-power supply
2020-12-18 Add functional pins handling
2020-12-18 Segregate decoupling capacitors
2020-12-20 Add decoupling capacitors placement and re-annotate
2020-12-21 Add DDR3 breakout and change its connection to FPGA
2020-12-21 Update RoT connector pinout
2020-12-22 Add USB host circuit
2020-12-23 Add PCIex4 clk signals filtration and standoff
2020-12-26 Add USB client and eMMC to schematic
2020-12-27 Add SPI Flash pin markings and connect SGPIO1_CLK
2020-12-27 Fix SGPIOlabels
2020-12-27 Fix VCC1V2 labels and add missing resistor
2020-12-28 Connect SPI0 to FPGA through 0R
2020-12-28 Add interface tabele and fix pin labels
2020-12-28 Add component placement
2020-12-28 Update diagram and visualisation
2020-12-28 Update component libraries
2020-12-29 Add user LEDs
2020-12-29 Fix power supply labels and power sequencing
2020-12-29 Update table and add minor changes
2020-12-29 Fix sequencing transistors connection
2020-12-29 Add 1nF capacitor
2020-12-29 Reconnect RGMII signals
2020-12-29 Update eeMMC flash
2020-12-29 Replace RJ45 connector to mid-plane
2020-12-30 Add USB3300-EZK-TR - USB host circuit
2020-12-30 Add second USB3300 IC - update table
2020-12-30 Library fix
2020-12-30 ETH pins moved to match ECPIX5. Added Eth reset circuit
2020-12-30 Changed DDR3 and mics if connections
2020-12-30 Add USB and PCIe routing
    Fix usb decoupling capacitors connection
    Replace 120k resistor with 12k
2020-12-30 Untangled SDRAM
2020-12-30 DDR 85% routed. Re-annotated duplicated components
2020-12-31 Add M.2 PCIe and RoT routing
2020-12-31 DDR pullupus
2020-12-31 Updated ECP symbol - n.c. fanned out
2020-12-31 Reconnect ULPI interfaces
2020-12-31 Add ULPI routing
2021-01-04 Edge conn fanout, RoT placement
2021-01-04 Update PDF schematic
2021-01-05 Routed NCSI chip corner
2021-01-07 Updated RoT connector
2021-01-07 ETH breakout
2021-01-07 ESPI routed
2021-01-07 Added 100MHz and PCLK markings on FPGA symbol
2021-01-07 Updated power supply sequencing and labels
2021-01-07 I3C routed
2021-02-03 Started sketching MMC
2021-02-03 Added mounting standoffs to schematics
2021-02-03 Fixed position of mounting holes
2021-02-03 Added voltage supply 0Rs and testpads, 0Rs for EN signals
2021-02-03 Power block routed, main power planes, started FPGA pwr connection
2021-02-03 I2C routed
2021-02-03 Changed eMMC chip, some components placed
2021-02-03 Add RGMII routig
2021-02-03 Add ethernet diff pairs routing
2021-02-03 Connect user LEDs to FPGA
2021-02-03 Adjusted FPGA cap placement
2021-02-03 Add user LEDs and JTAG routing
2021-02-03 UART routed, fixed ESPI pins
2021-02-03 eMMC routed
2021-02-03 Power supply components arranged
2021-02-03 Edge power connected, resized all vias
2021-02-03 initial connections of orphan signals
2021-02-03 DDR group 0 (DQ0-7) tuned
2021-02-03 Fix diff pairs dimensions
2021-02-03 Add miscellaneous routing
2021-02-03 Add decoupling routing - WIP
2021-02-03 Routed programming mode circuit
2021-02-03 DDR group 1 (DQ8-15) tuned
2021-02-03 Clean up top designators and DRC errors
2021-02-03 Added 2.5V and 1.0V planes
2021-02-03 FPGA power connection and decoupling
2021-02-03 Fixed DDR DRC errors
2021-02-03 Finish routing and fix some drc - WIP
2021-02-03 Clean up bottom designators -WIP
2021-02-03 Add misc signals routing
2021-02-03 DDR3 power and decoupling
2021-02-03 5V0 and 1V8 domains defined
2021-02-03 routed power indicators
2021-02-03 Fix drc errors
    -Add 0.15mm traces spacing
    -Fix Power planes at VCC2
    -Add keepout areas
2021-02-03 Fixed 1V0 converter. Some minor signal routed
2021-02-03 Add FTDI placement and routing
2021-02-03 Update FTDI routing
2021-02-03 Silkscreen references arranged
2021-02-03 DDR address group tuned
2021-02-03 Update FTDI schematic
2021-02-03 Moved PS blockto accomodate clearance
2021-02-03 Add JTAG/FTDI to schematic
2021-02-03 Fixed 1.8V supplies on USB hosts
2021-02-03 FTDI/JTAG updated, connector added
2021-02-03 Move components from keep-out areas
2021-02-03 Clean designators and add missing components
2021-02-03 Replaced ROT connector, added more communication pins, connected to FPGA
2021-02-03 Update micro USB 3d model and add vbus decoupling
2021-02-03 Add logos and via stitching
2021-02-03 Added silkscreen markings on J7 and J8
2021-02-03 Added local libs
2021-02-03 updated MMC pullups to 33k
2021-02-03 Fixes to power sequencer on layout
2021-02-03 RoT standoff and connector adjust
2021-02-03 MMC CLK pullup fix
2021-02-03 Fixed edge connector and TPM connector footprints
2021-02-03 Designators cleanup
2021-02-03 Replaced USB controllers oscillators
2021-02-03 Fixes to power sequencer circuit
2021-02-03 updated eMMC layout
2021-02-03 Replaced PHY oscillator with MEMS
2021-02-03 Fixed PHY pullups
2021-02-03 Added AUX supply and replaced battery connector
2021-02-03 PCIe net name and routing fix
2021-02-03 9774040151 fix
2021-02-03 Connected missing TPM signals
2021-02-03 Fix in PCIe signal labels and differential pairs width
2021-02-03 Resolve DRC
2021-02-03 Reduced redundant buried via layer pairs
2021-02-03 Fix in 9774025151
2021-02-03 Tune the length of the RGMII traces
2021-02-03 Optimize RGMII RX capacitors
2021-02-03 Fixes to PCIe, orphaned signals, eMMC pullups
2021-02-03 Added some random GND stiching in empty areas
2021-02-03 Adjusted power sequencer circuit
2021-02-03 Fixed designators
2021-02-03 Bumped revision to 1.0.1
2021-02-03 Changed polarity of ETH_LEDx
2021-02-03 Bump release to 1.0.2
2021-02-03 Bump release to 1.0.3
2021-02-03 Production release
2021-05-01 Notes added by 'git notes add'
2021-05-03 Add copyrights to LICENSE
2021-05-21 new diagram
2021-05-21 Add new diagram
2021-10-07 Update 3D Vis
2021-10-07 Add stackup info on Fabrication layer
2021-10-07 Cleanup
2021-11-03 Add PCB stackup table
2021-11-03 Change PCIe track width
2022-05-27 Add badge
2022-09-26 Bump revision to 1.1.0
2022-09-26 Fix I2C5 and PCIE connections on J5 (schematic and library symbol fix)
2022-09-26 Reroute I2C5, PCIE and GND on J9, update footprint
2022-09-28 Update PDF schematics
2023-02-20 README: Add photo
2024-07-22 Port to Kicad 6.0 and small fixes
    Migrated local library to Kicad 6.0
    Loclib
    Rev bump to 1.2.0
    README: Add photo
2024-07-22 [#61392] Convert project to KiCad 7
    [#61392] Run globlib
    [#61392] Allign components to the grid
    [#61392] Update oshw and antmicro logo
    [#61392] Standarize ethernet sheet
    [#61392] Standarize pcie-conn sheet
    [#61392] Standarize rot sheet
2024-07-22 [#61392] Import changes to the PCB
    [#61392] Fix D2 orientation
    [#61392] Fix J2 J1 D6 orientation
    [#61392] WIP: PCB Fix caps orienations
    [#61392] PCB Fix caps orienations
    [#61392] Fix missalligned edge cuts
    [#61392] Sync Sch with PCB
2024-07-22 [#62567] HTSSOP-20 fix

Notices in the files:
parts and their libraries:
Copyright 2016 Accelerated Designs. All rights reserved.
